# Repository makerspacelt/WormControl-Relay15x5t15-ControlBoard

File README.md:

---

WormControl Relay Control boards

Dev NOTE: before commit, run `./kibot.sh` to regenerate documentation, bom, gerbers and other assets.

* [schematics.pdf](gen/schematics.pdf)
* [pcb.pdf with dimensions](gen/pcb.pdf)
* [ibom.html](gen/single/ibom.html)

---

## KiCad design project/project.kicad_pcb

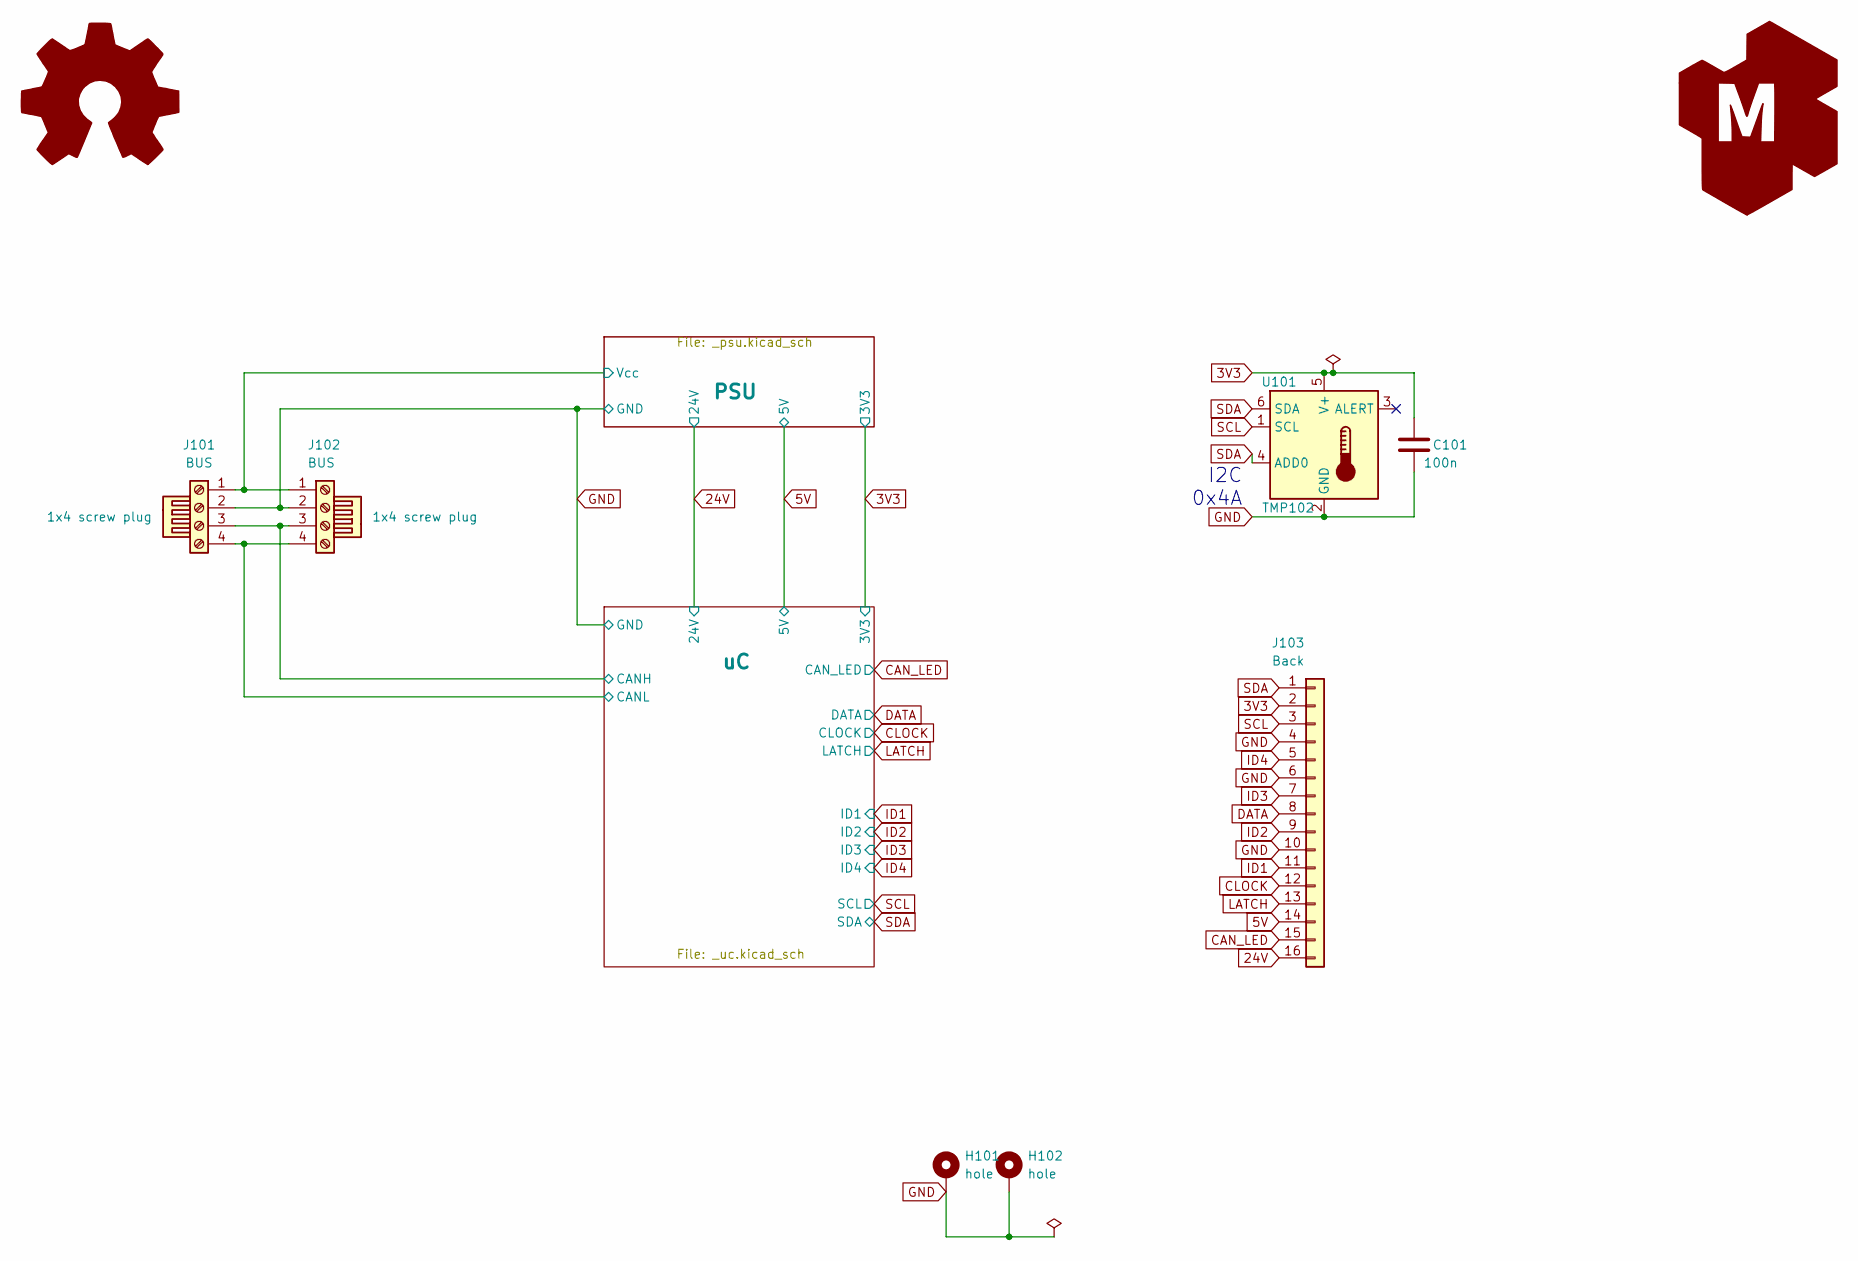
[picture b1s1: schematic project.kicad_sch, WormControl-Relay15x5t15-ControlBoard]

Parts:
BOM101, BOM102: 1x4 screw plug; jlc-part-type E
C101: 100n; C_0805_2012Metric_Pad1.18x1.45mm_HandSolder; jlc-part-type B
G101: Logo_Open_Hardware_Large; OSHW-Symbol_6.7x6mm_SilkScreen
G102: LOGO_KMS; logo_kms_small_silkscreen
H101, H102: hole; MountingHole_3.2mm_M3_Pad_Via
J101, J102: BUS; PhoenixContact_MCV_1,5_4-G-3.5_1x04_P3.50mm_Vertical; jlc-part-type E
J103: Back; PinSocket_2x08_P2.54mm_Vertical_SMD; lcsc# C3975153
U101: TMP102; SOT-563; jlc-part-type E

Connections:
3V3: C101.1, J103.2, U101.5 (V+); also elsewhere on the board
5V: J103.14; also elsewhere on the board
24V: J103.16; also elsewhere on the board
/PSU/Vcc: J101.1, J102.1; also elsewhere on the board
/uC/CANH: J101.3, J102.3; also elsewhere on the board
/uC/CANL: J101.4, J102.4; also elsewhere on the board
CAN_LED: J103.15; also elsewhere on the board
CLOCK: J103.12; also elsewhere on the board
DATA: J103.8; also elsewhere on the board
GND: C101.2, H101.1, H102.1, J101.2, J102.2, J103.4, J103.6, J103.10, U101.2 (GND); also elsewhere on the board
ID1: J103.11; also elsewhere on the board
ID2: J103.9; also elsewhere on the board
ID3: J103.7; also elsewhere on the board
ID4: J103.5; also elsewhere on the board
LATCH: J103.13; also elsewhere on the board
SCL: J103.3, U101.1 (SCL); also elsewhere on the board
SDA: J103.1, U101.4 (ADD0), U101.6 (SDA); also elsewhere on the board

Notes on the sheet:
I2C 0x4A

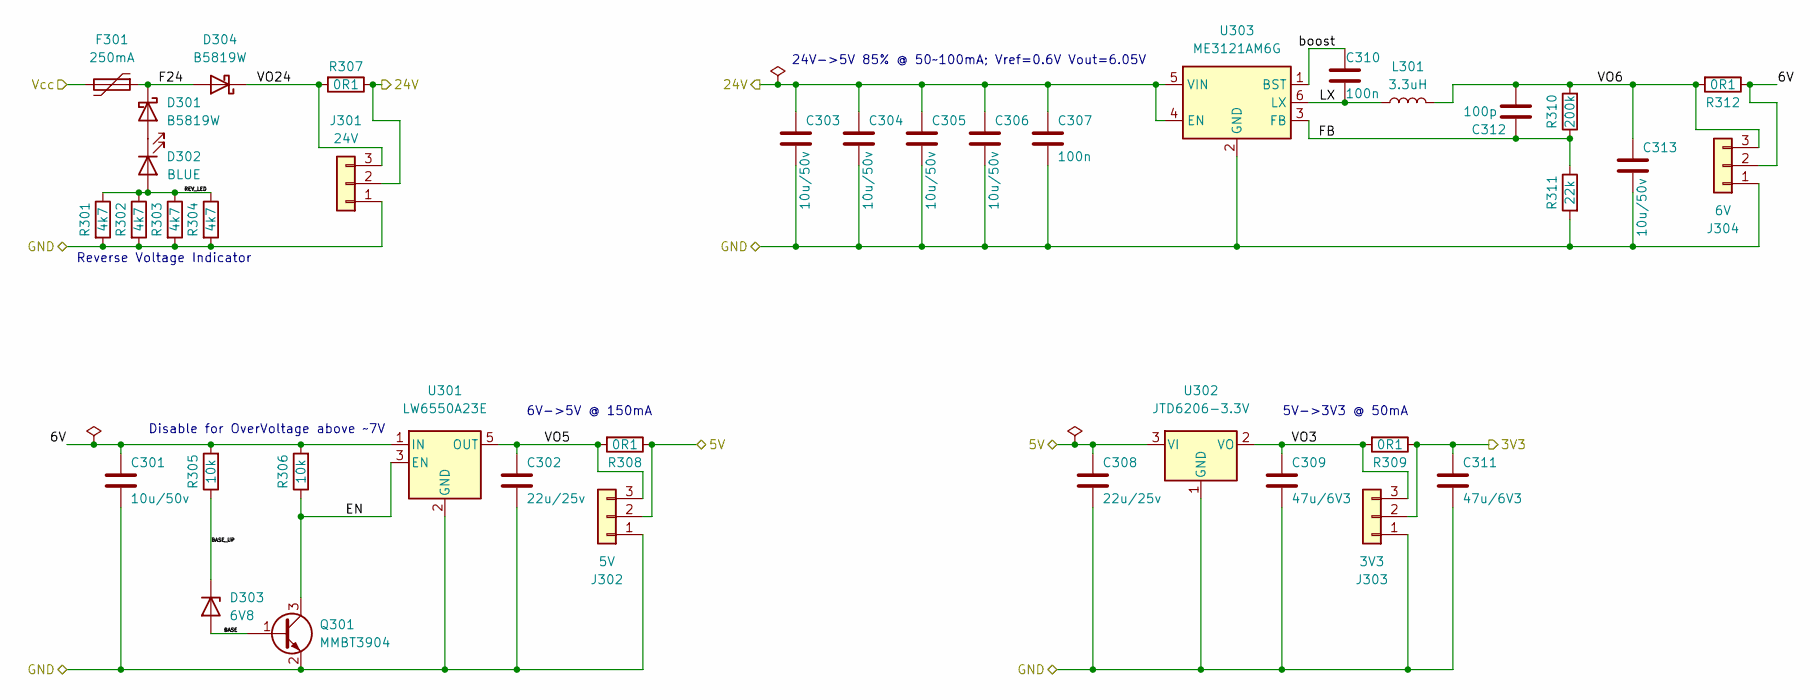
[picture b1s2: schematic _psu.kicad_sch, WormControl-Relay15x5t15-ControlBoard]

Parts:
C301, C303, C304, C305, C306, C313: 10u/50v; C_0805_2012Metric_Pad1.18x1.45mm_HandSolder; jlc-part-type B
C302, C308: 22u/25v; C_0805_2012Metric_Pad1.18x1.45mm_HandSolder; jlc-part-type B
C307, C310: 100n; C_0805_2012Metric_Pad1.18x1.45mm_HandSolder; jlc-part-type B
C309, C311: 47u/6V3; C_0805_2012Metric_Pad1.18x1.45mm_HandSolder; jlc-part-type B
C312: 100p; C_0805_2012Metric_Pad1.18x1.45mm_HandSolder; jlc-part-type B
D301, D304: B5819W; D_SOD-123; jlc-part-type B
D302: BLUE; LED_0805_2012Metric_Pad1.15x1.40mm_HandSolder; jlc-part-type B
D303: 6V8; D_SOD-323_HandSoldering; jlc-part-type E
F301: 250mA; Fuse_0805_2012Metric_Pad1.15x1.40mm_HandSolder; lcsc# C22378353
J301: 24V; PinHeader_1x03_P2.54mm_Vertical
J302: 5V; PinHeader_1x03_P2.54mm_Vertical
J303: 3V3; PinHeader_1x03_P2.54mm_Vertical
J304: 6V; PinHeader_1x03_P2.54mm_Vertical
L301: 3.3uH; L_1008_2520Metric_Pad1.43x2.20mm_HandSolder; jlc-part-type E
Q301: MMBT3904; SOT-23; jlc-part-type B
R301, R302, R303, R304: 4k7; R_0805_2012Metric_Pad1.20x1.40mm_HandSolder; jlc-part-type B
R305, R306: 10k; R_0805_2012Metric_Pad1.20x1.40mm_HandSolder; jlc-part-type B
R307, R308, R309, R312: 0R1; R_0805_2012Metric_Pad1.20x1.40mm_HandSolder; jlc-part-type E
R310: 200k; R_0805_2012Metric_Pad1.20x1.40mm_HandSolder; jlc-part-type B
R311: 22k; R_0805_2012Metric_Pad1.20x1.40mm_HandSolder; jlc-part-type B
U301: LW6550A23E; SOT-23-5; jlc-part-type E
U302: JTD6206-3.3V; SOT-23; jlc-part-type B
U303: ME3121AM6G; SOT-23-6; jlc-part-type E

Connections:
3V3: C311.1, J303.2, R309.1; also elsewhere on the board
5V: C308.1, J302.2, R308.1, U302.3 (VI); also elsewhere on the board
24V: C303.1, C304.1, C305.1, C306.1, C307.1, J301.2, R307.1, U303.4 (EN), U303.5 (VIN); also elsewhere on the board
/PSU/6V: C301.1, J304.2, R305.2, R306.2, R312.1, U301.1 (IN)
/PSU/BASE: D303.2 (A), Q301.1 (B)
/PSU/BASE_UP: D303.1 (K), R305.1
/PSU/EN: Q301.3 (C), R306.1, U301.3 (EN)
/PSU/F24: D301.1 (K), D304.2 (A), F301.1
/PSU/FB: C312.1, R310.1, R311.1, U303.3 (FB)
/PSU/LX: C310.2, L301.1, U303.6 (LX)
/PSU/REV_LED: D302.2 (A), R301.1, R302.1, R303.1, R304.1
/PSU/VO3: C309.1, J303.3, R309.2, U302.2 (VO)
/PSU/VO5: C302.1, J302.3, R308.2, U301.5 (OUT)
/PSU/VO6: C312.2, C313.1, J304.3, L301.2, R310.2, R312.2
/PSU/VO24: D304.1 (K), J301.3, R307.2
/PSU/Vcc: F301.2; also elsewhere on the board
/PSU/boost: C310.1, U303.1 (BST)
GND: C301.2, C302.2, C303.2, C304.2, C305.2, C306.2, C307.2, C308.2, C309.2, C311.2, C313.2, J301.1, J302.1, J303.1, J304.1, Q301.2 (E), R301.2, R302.2, R303.2, R304.2, R311.2, U301.2 (GND), U302.1 (GND), U303.2 (GND); also elsewhere on the board
unnamed: D301.2 (A), D302.1 (K)

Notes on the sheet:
24V->5V 85% @ 50~100mA; Vref=0.6V Vout=6.05V
5V->3V3 @ 50mA
Reverse Voltage Indicator
6V->5V @ 150mA
Disable for OverVoltage above ~7V

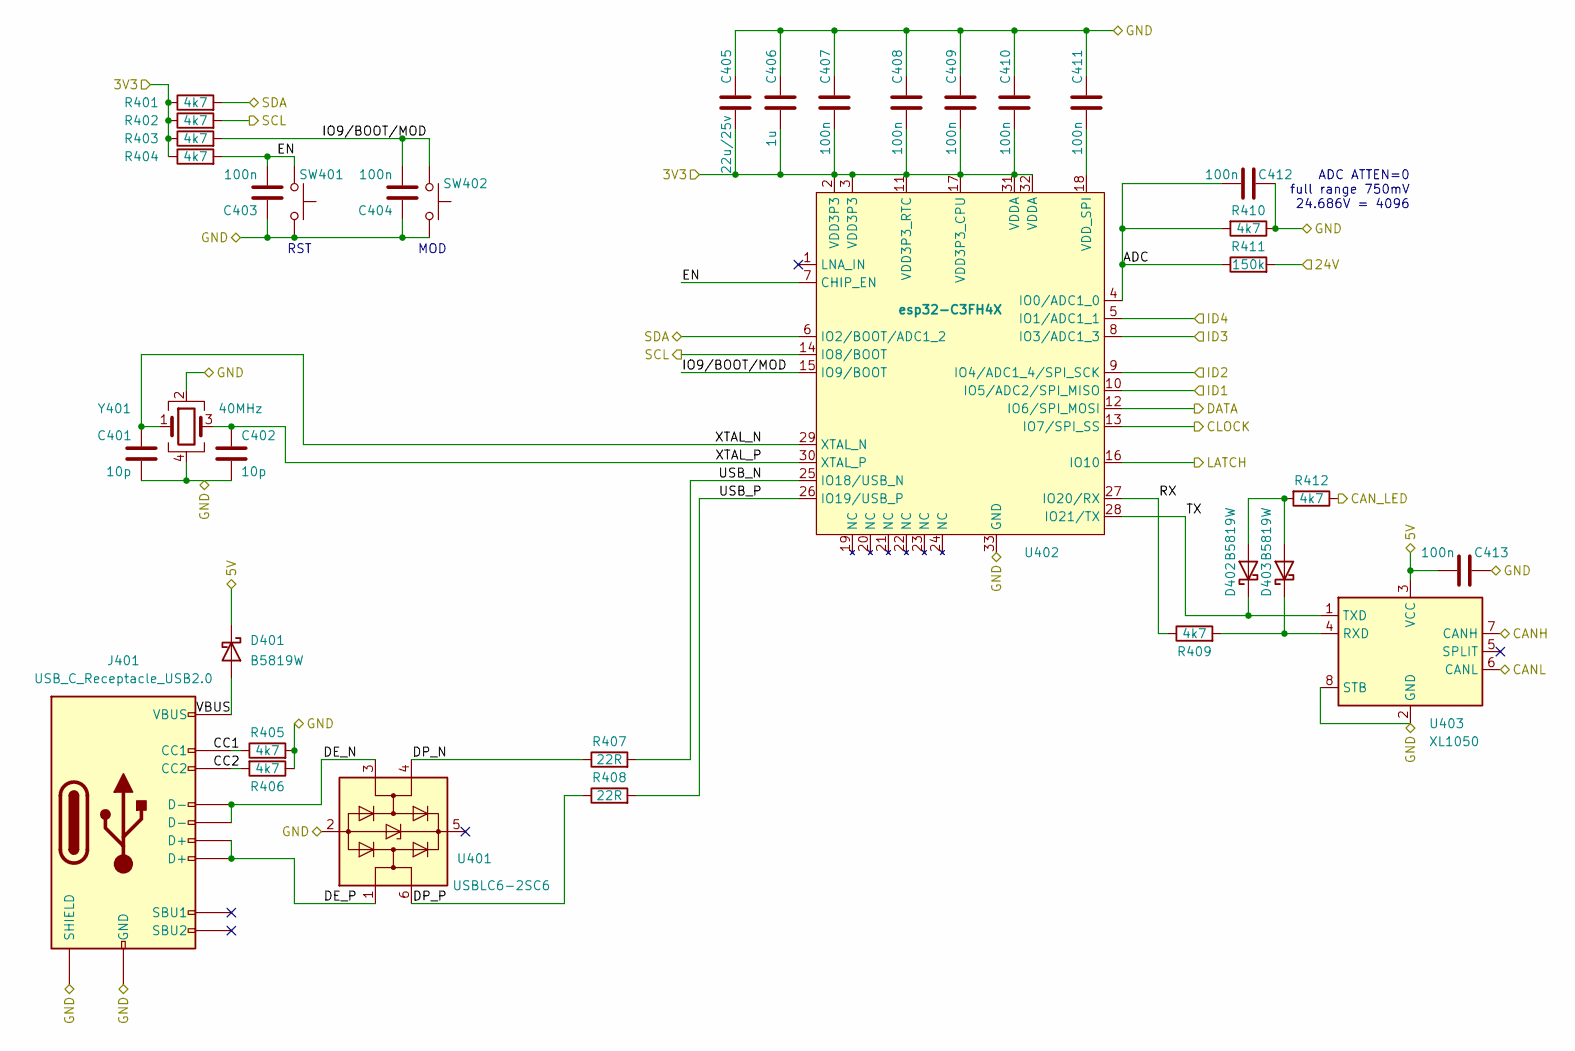
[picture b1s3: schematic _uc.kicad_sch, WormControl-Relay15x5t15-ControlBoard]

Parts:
C401, C402: 10p; C_0805_2012Metric_Pad1.18x1.45mm_HandSolder; jlc-part-type B
C403, C404, C407, C408, C409, C410, C411, C412, C413: 100n; C_0805_2012Metric_Pad1.18x1.45mm_HandSolder; jlc-part-type B
C405: 22u/25v; C_0805_2012Metric_Pad1.18x1.45mm_HandSolder; jlc-part-type B
C406: 1u; C_0805_2012Metric_Pad1.18x1.45mm_HandSolder; jlc-part-type B
D401, D402, D403: B5819W; D_SOD-123; jlc-part-type B
J401: USB_C_Receptacle_USB2.0; USB_C_Receptacle_G-Switch_GT-USB-7082G; jlc-part-type E
R401, R402, R403, R404, R405, R406, R409, R410, R412: 4k7; R_0805_2012Metric_Pad1.20x1.40mm_HandSolder; jlc-part-type B
R407, R408: 22R; R_0805_2012Metric_Pad1.20x1.40mm_HandSolder; jlc-part-type B
R411: 150k; R_0805_2012Metric_Pad1.20x1.40mm_HandSolder; jlc-part-type B
SW401, SW402: 15mm; SW_SPST_15; jlc-part-type E
U401: USBLC6-2SC6; SOT-23-6; jlc-part-type E
U402: esp32-C3FH4X; QFN-32-1EP_5x5mm_P0.5mm_EP3.65x3.65mm; jlc-part-type E
U403: XL1050; SOIC-8_3.9x4.9mm_P1.27mm; jlc-part-type E
Y401: 40MHz; Crystal_SMD_2016-4Pin_2.0x1.6mm; jlc-part-type E

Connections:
3V3: C405.2, C406.2, C407.1, C408.1, C409.1, C410.1, R401.1, R402.1, R403.1, R404.1, U402.2 (VDD3P3), U402.3 (VDD3P3), U402.11 (VDD3P3_RTC), U402.17 (VDD3P3_CPU), U402.31 (VDDA), U402.32 (VDDA); also elsewhere on the board
5V: C413.1, D401.1 (K), U403.3 (VCC); also elsewhere on the board
24V: R411.2; also elsewhere on the board
/uC/ADC: C412.1, R410.2, R411.1, U402.4 (IO0/ADC1_0)
/uC/CANH: U403.7 (CANH); also elsewhere on the board
/uC/CANL: U403.6 (CANL); also elsewhere on the board
/uC/CC1: J401.A5 (CC1), R405.1
/uC/CC2: J401.B5 (CC2), R406.2
/uC/DE_N: J401.A7 (D-), J401.B7 (D-), U401.3 (I/O2)
/uC/DE_P: J401.A6 (D+), J401.B6 (D+), U401.1 (I/O1)
/uC/DP_N: R407.1, U401.4 (I/O2)
/uC/DP_P: R408.1, U401.6 (I/O1)
/uC/EN: C403.2, R404.2, SW401.1, U402.7 (CHIP_EN)
/uC/IO9/BOOT/MOD: C404.2, R403.2, SW402.1, U402.15 (IO9/BOOT)
/uC/RX: R409.1, U402.27 (IO20/RX)
/uC/TX: D402.1 (K), U402.28 (IO21/TX), U403.1 (TXD)
/uC/USB_N: R407.2, U402.25 (IO18/USB_N)
/uC/USB_P: R408.2, U402.26 (IO19/USB_P)
/uC/VBUS: D401.2 (A), J401.A4 (VBUS), J401.A9 (VBUS), J401.B4 (VBUS), J401.B9 (VBUS)
/uC/XTAL_N: C401.1, U402.29 (XTAL_N), Y401.1
/uC/XTAL_P: C402.1, U402.30 (XTAL_P), Y401.3
CAN_LED: R412.1; also elsewhere on the board
CLOCK: U402.13 (IO7/SPI_SS); also elsewhere on the board
DATA: U402.12 (IO6/SPI_MOSI); also elsewhere on the board
GND: C401.2, C402.2, C403.1, C404.1, C405.1, C406.1, C407.2, C408.2, C409.2, C410.2, C411.2, C412.2, C413.2, J401.A1 (GND), J401.A12 (GND), J401.B1 (GND), J401.B12 (GND), J401.S1 (SHIELD), R405.2, R406.1, R410.1, SW401.2, SW402.2, U401.2 (GND), U402.33 (GND), U403.2 (GND), U403.8 (STB), Y401.2, Y401.4; also elsewhere on the board
ID1: U402.10 (IO5/ADC2/SPI_MISO); also elsewhere on the board
ID2: U402.9 (IO4/ADC1_4/SPI_SCK); also elsewhere on the board
ID3: U402.8 (IO3/ADC1_3); also elsewhere on the board
ID4: U402.5 (IO1/ADC1_1); also elsewhere on the board
LATCH: U402.16 (IO10); also elsewhere on the board
unnamed: C411.1, U402.18 (VDD_SPI)
unnamed: D402.2 (A), D403.2 (A), R412.2
unnamed: D403.1 (K), R409.2, U403.4 (RXD)
SCL: R402.2, U402.14 (IO8/BOOT); also elsewhere on the board
SDA: R401.2, U402.6 (IO2/BOOT/ADC1_2); also elsewhere on the board

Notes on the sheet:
RST
ADC ATTEN=0 full range 750mV 24.686V = 4096
MOD

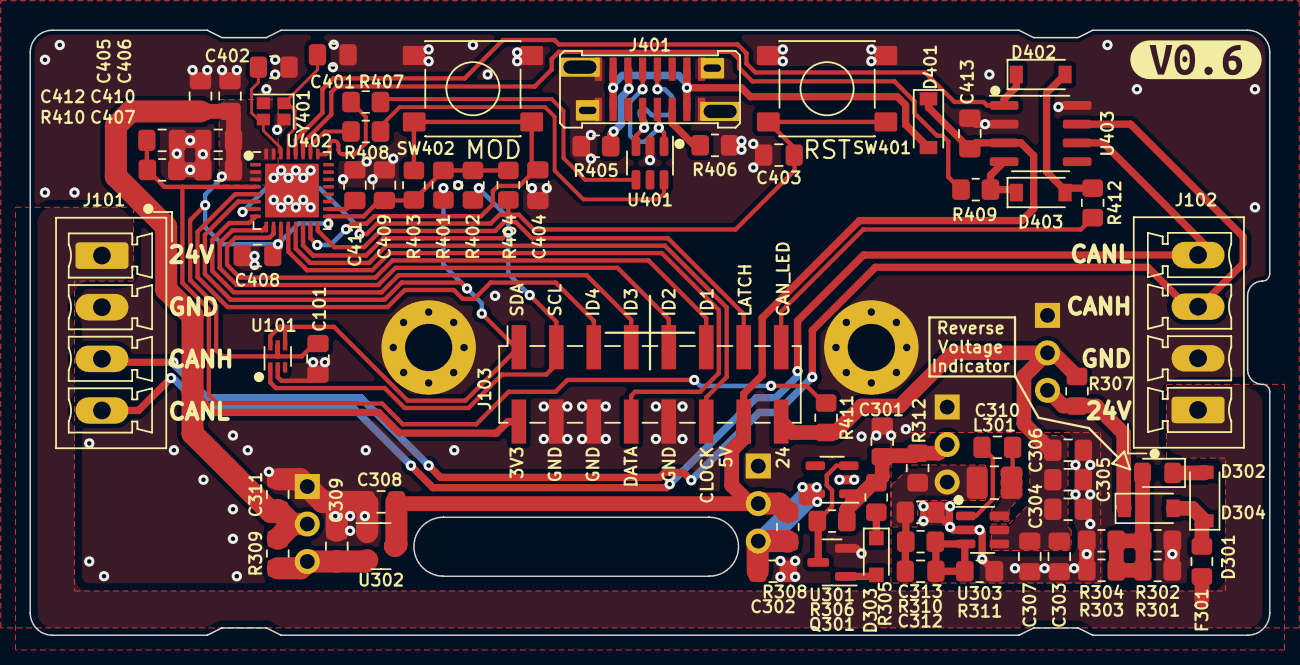
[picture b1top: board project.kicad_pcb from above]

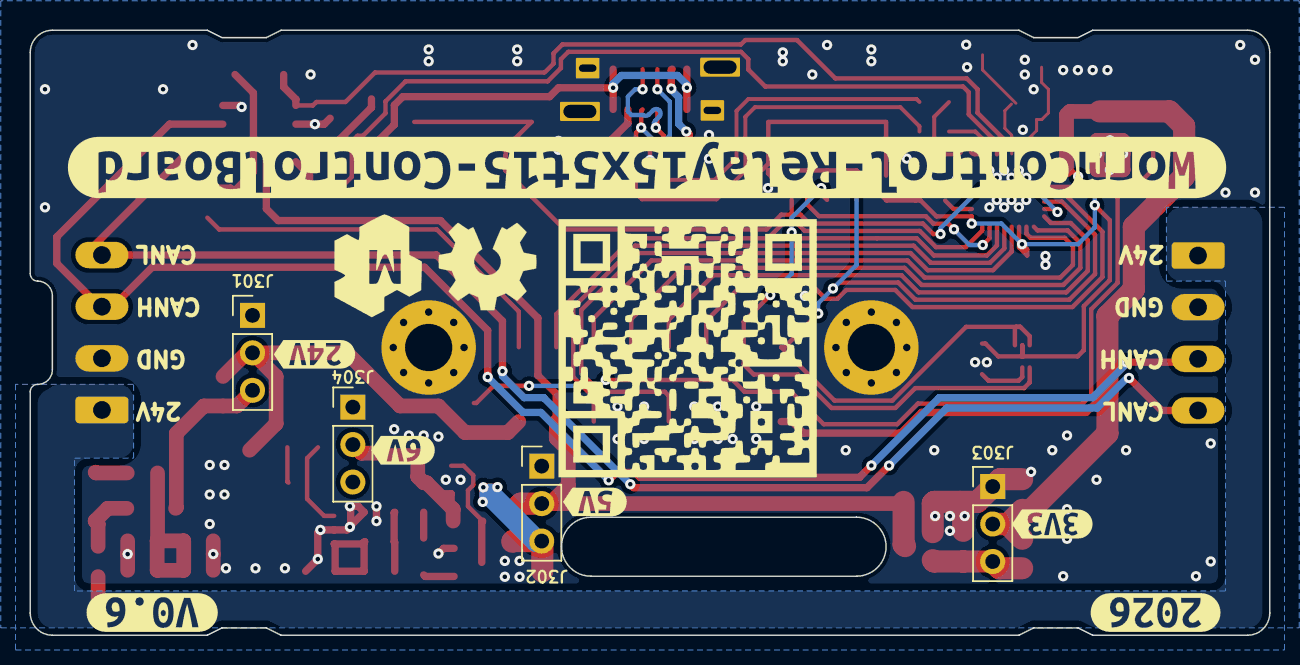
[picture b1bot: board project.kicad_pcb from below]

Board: 4 copper layers, 84.0 x 41.0 mm, 91 parts (13 on the bottom side), 50 nets.

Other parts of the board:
kibuzzard-68F6C7D9: G***; kibuzzard-68F6C7D9
kibuzzard-68F6C8CD: G***; kibuzzard-68F6C8CD
kibuzzard-68F6C776: G***; kibuzzard-68F6C776
kibuzzard-68F6C793: G***; kibuzzard-68F6C793
kibuzzard-69BC0AB9: G***; kibuzzard-69BC0AB9
kibuzzard-69BC0BA6: G***; kibuzzard-69BC0BA6
kibuzzard-69E60A07: G***; kibuzzard-69E60A07
kibuzzard-69E609FA: G***; kibuzzard-69E609FA

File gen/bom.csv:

"Row","Description","Part","References","Value","Footprint","Quantity Per PCB","Status","Datasheet","lcsc#","jlc-part-type","alt#"
"1","Heatsink","Heatsink","BOM101,BOM102","1x4 screw plug","","2"," ","https://www.lcsc.com/datasheet/lcsc_datasheet_2309070925_DEG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","C7603442","E",""
"2","Unpolarized capacitor","C","C401,C402","10p","C_0805_2012Metric_Pad1.18x1.45mm_HandSolder","2"," ","https://www.lcsc.com/datasheet/lcsc_datasheet_2304140030_Sam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","C1634","B",""
"3","Unpolarized capacitor","C","C312","100p","C_0805_2012Metric_Pad1.18x1.45mm_HandSolder","1"," ","https://www.lcsc.com/datasheet/lcsc_datasheet_2304140030_Sam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","C1790","B",""
"4","Unpolarized capacitor","C","C101,C307,C310,C403,C404,C407,C408,C409,C410,C411,C412,C413","100n","C_0805_2012Metric_Pad1.18x1.45mm_HandSolder","12"," ","https://www.lcsc.com/datasheet/lcsc_datasheet_2304140030_Sam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","C28233","B",""
"5","Unpolarized capacitor","C","C406","1u","C_0805_2012Metric_Pad1.18x1.45mm_HandSolder","1"," ","https://www.lcsc.com/datasheet/lcsc_datasheet_2304140030_Sam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","C28323","B",""
"6","Unpolarized capacitor","C","C301,C303,C304,C305,C306,C313","10u/50v","C_0805_2012Metric_Pad1.18x1.45mm_HandSolder","6"," ","https://www.lcsc.com/datasheet/lcsc_datasheet_2411041759_Mur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","C440198","B",""
"7","Unpolarized capacitor","C","C302,C308,C405","22u/25v","C_0805_2012Metric_Pad1.18x1.45mm_HandSolder","3"," ","https://www.lcsc.com/datasheet/lcsc_datasheet_2304140030_Sam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","C45783","B",""
"8","Unpolarized capacitor","C","C309,C311","47u/6V3","C_0805_2012Metric_Pad1.18x1.45mm_HandSolder","2"," ","https://www.lcsc.com/datasheet/lcsc_datasheet_2304140030_Sam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","C16780","B",""
"9","Zener diode","D_Zener","D303","6V8","D_SOD-323_HandSoldering","1"," ","https://www.lcsc.com/datasheet/C123062.pdf","C123062","E",""
"10","Schottky diode","D_Schottky","D301,D304,D401,D402,D403","B5819W","D_SOD-123","5"," ","https://www.lcsc.com/datasheet/lcsc_datasheet_2304140030_Jia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","C8598","B",""
"11","Light emitting diode","LED","D302","BLUE","LED_0805_2012Metric_Pad1.15x1.40mm_HandSolder","1"," ","https://jlcpcb.com/api/file/downloadByFileSystemAccessId/855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","C2297","B",""
"12","Resettable fuse, polymeric positive temperature coefficient","Polyfuse","F301","250mA","Fuse_0805_2012Metric_Pad1.15x1.40mm_HandSolder","1"," ","https://wmsc.lcsc.com/wmsc/upload/file/pdf/v2/lcsc/240408162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","C22378353","E",""
"13","Generic connector, single row, 01x03, script generated (kicad-library-utils/schlib/autogen/connector/)","Conn_01x03","J301,J302,J303,J304","24V","PinHeader_1x03_P2.54mm_Vertical","4"," ","~","","-",""
"14","Generic screw terminal, single row, 01x04, script generated (kicad-library-utils/schlib/autogen/connector/)","Screw_Terminal_01x04","J101,J102","BUS","PhoenixContact_MCV_1,5_4-G-3.5_1x04_P3.50mm_Vertical","2"," ","https://www.lcsc.com/datasheet/lcsc_datasheet_2304140030_Nin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","C880556","E",""
"15","Generic connector, single row, 01x16, script generated (kicad-library-utils/schlib/autogen/connector/)","Conn_01x16","J103","Back","PinSocket_2x08_P2.54mm_Vertical_SMD","1"," ","https://wmsc.lcsc.com/wmsc/upload/file/pdf/v2/lcsc/230609101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","C3975153","E",""
"16","USB 2.0-only Type-C Receptacle connector","USB_C_Receptacle_USB2.0","J401","USB_C_Receptacle_USB2.0","USB_C_Receptacle_G-Switch_GT-USB-7082G","1"," ","https://www.lcsc.com/datasheet/lcsc_datasheet_2405271642_G-S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","C22383836","E",""
"17","Inductor","L","L301","3.3uH","L_1008_2520Metric_Pad1.43x2.20mm_HandSolder","1"," ","https://www.lcsc.com/datasheet/C5832373.pdf","C5832373","E",""
"18","NPN transistor, base/emitter/collector","Q_NPN_BEC","Q301","MMBT3904","SOT-23","1"," ","https://www.lcsc.com/datasheet/C20526.pdf","C20526","B",""
"19","Resistor","R","R307,R308,R309,R312","0R1","R_0805_2012Metric_Pad1.20x1.40mm_HandSolder","4"," ","https://www.lcsc.com/datasheet/lcsc_datasheet_2304140030_UNI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","C127687","E",""
"20","Resistor","R","R407,R408","22R","R_0805_2012Metric_Pad1.20x1.40mm_HandSolder","2"," ","~","C17561","B",""
"21","Resistor","R","R301,R302,R303,R304,R401,R402,R403,R404,R405,R406,R409,R410,R412","4k7","R_0805_2012Metric_Pad1.20x1.40mm_HandSolder","13"," ","~","C17673","B",""
"22","Resistor","R","R305,R306","10k","R_0805_2012Metric_Pad1.20x1.40mm_HandSolder","2"," ","~","C17414","B",""
"23","Resistor","R","R311","22k","R_0805_2012Metric_Pad1.20x1.40mm_HandSolder","1"," ","~","C17560","B",""
"24","Resistor","R","R411","150k","R_0805_2012Metric_Pad1.20x1.40mm_HandSolder","1"," ","~","C17470","B",""
"25","Resistor","R","R310","200k","R_0805_2012Metric_Pad1.20x1.40mm_HandSolder","1"," ","~","C17539","B",""
"26","Push button switch, generic, two pins","SW_Push","SW401,SW402","15mm","SW_SPST_15","2"," ","https://www.lcsc.com/datasheet/lcsc_datasheet_2110120830_XKB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","C2885154","E",""
"27","300mA Low Dropout Voltage Regulator, Fixed Output 3.3V, SOT-23","APE8865N-33-HF-3","U302","JTD6206-3.3V","SOT-23","1"," ","https://www.lcsc.com/datasheet/C42443428.pdf","C5446","B","C42443428"
"28","300mA Low Dropout Voltage Regulator, Fixed Output 0.9V, SOT-23-5","TLV71209_SOT23-5","U301","LW6550A23E","SOT-23-5","1"," ","https://www.lcsc.com/datasheet/C20754712.pdf","C20754712","E",""
"29","1.2 A Simple Buck Regulator, 3-26V input, 1.5Mhz","AOZ1280CI","U303","ME3121AM6G","SOT-23-6","1"," ","https://m.huazhoucn.com/upFiles/common/2022/12/ME3121_Series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","C2932938","E",""
"30","Digital Temperature Sensor, +/- 3 °C, low-Power, SMBus, 12 bit, Two-Wire Serial Interface, SOT-563","TMP102xxDRL","U101","TMP102","SOT-563","1"," ","https://www.ti.com/lit/ds/symlink/tmp102.pdf","C99269","E",""
"31","Very low capacitance ESD protection diode, 2 data-line, SOT-23-6","USBLC6-2SC6","U401","USBLC6-2SC6","SOT-23-6","1"," ","https://www.lcsc.com/datasheet/lcsc_datasheet_2311091738_UMW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","C2687116","E",""
"32","High-Speed CAN Transceiver, standby mode, split pin, SOIC-8","TJA1042T","U403","XL1050","SOIC-8_3.9x4.9mm_P1.27mm","1"," ","https://www.lcsc.com/datasheet/lcsc_datasheet_2309141025_XIN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","C609746","E",""
"33","esp32-C3FH4X 4MB flash QFN32-1EP 5x5mm EP3.7x3.7mm","esp32-C3FH4X","U402","esp32-C3FH4X","QFN-32-1EP_5x5mm_P0.5mm_EP3.65x3.65mm","1"," ","https://www.espressif.com/sites/default/files/documentation/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","C2858491","E",""
"34","Four pin crystal, GND on pins 2 and 4","Crystal_GND24","Y401","40MHz","Crystal_SMD_2016-4Pin_2.0x1.6mm","1"," ","https://www.lcsc.com/datasheet/C20885029.pdf","C20885029","E",""

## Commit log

2026-03-19 spritting up boards into separate repos
2026-03-19 part consolidation and QoL improvements
    * Using same crystal as in other projects
    * Switching to TMP102 as TMP101 is no longer available
    * Adding cutouts to make assembly esier
    * Making net names more readable
    * bumping up version
2026-03-19 adding cutout for easier assembly
2026-04-20 fixing tmp102 pinout
